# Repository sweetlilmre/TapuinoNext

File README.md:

# TapuinoNext

## Intro

Welcome to the TapuinoNext alpha.  

Most of the code has been written and tested to a fair extent, but there are bound to be loads of bugs.
Please report bugs as issues against the repo. If you have fixes, please submit these as a pull request.
I could really use some help with documentation in markdown format if you would like to contribute in that way.

## Using the TapuinoNext

Instructions on how to navigate the UI and detail on the TapuinoNext functionality can be found on this page: [TapuinoNext UI](docs/ui/TapuinoNext-UI.md). This is still very much a work in progress.

## Hardware

- "instructions" to build a stripboard prototype are available at [Prototype Build](docs/PrototypeBuild.md)
- schematics and board designs for reference implementations are available in the [Eagle](docs/Eagle) folder.
- the mini board has been produced and tested successfully!
- **NB: the micro board has not**

The BOM for the TapuinoNext is:
- ESP32 Devkit equivalent: e.g. https://www.banggood.com/ESP32-WiFi-+-bluetooth-Development-Board-Ultra-Low-Power-Consumption-Dual-Core-ESP-32-ESP-32S-Similar-ESP8266-Geekcreit-for-Arduino-products-that-work-with-official-Arduino-boards-p-1175488.html

- resistors:
  - (voltage divider)
    - 1k5
    - 3k3
  - 100 Ohm (Recording LED current limiter)
- Rotary encoder KY-040: e.g. https://www.banggood.com/5Pcs-5V-KY-040-Rotary-Encoder-Module-AVR-PIC-p-951151.html

- LCD screen: SSD1306 OLED or HD44780 via I2C backpack
- SD Card breakout board / socket, no level shifter! Ones without resistors seem to work better. I used something like this: https://www.mischianti.org/2019/12/15/how-to-use-sd-card-with-esp8266-and-arduino/
This is the one I built:

- Bi-directional level shifter: e.g. https://www.banggood.com/10Pcs-Logic-Level-Converter-Bi-Directional-IIC-4-Way-Level-Conversion-Module-p-1033750.html

- C64 Datasette connector (use one off of a dead datasette or find one of these: https://www.thefuturewas8bit.com/cassette-port-connector-vic20-64-64c-128-128d-pet.html)

Wire this all up according to the schematic and flash the firmware.

## Firmware

If you have already flashed a recent firmware, then firmware releases are available at: https://github.com/sweetlilmre/TapuinoNext/releases

As newer firmware can self update, all you need to do is drop the *update.bin* file onto the root of the SD Card and select the firmware update option from the options menu.

For a first time build:

There is now an alternative to building the code and flashing.
- Download the latest `update.factory.bin` from the [TapuinoNext Releases Page ](https://github.com/sweetlilmre/TapuinoNext/releases)
- Using Google Chrome, go to the [Adafruit ESP Tool](https://adafruit.github.io/Adafruit_WebSerial_ESPTool/) page.
- Connect your ESP32 to your machine and make sure the drivers are installed
- Click "Connect" on the Adafruit page and select the COM port of your ESP32
- If the connect succeeds, you should see several `Choose a file...` buttons
- Click the first one, navigate to and select the `update.factory.bin` file you downloaded
- Click `Program`
- A progress bar will appear, once this is complete you should be good to go

Probably the easiest way to handle this at the moment is to:
- install VS Code
- install Platformio on top of that
- install the Espressif 32 platform or start a new project and choose "Espressif ESP32 Dev Module" as the board, with "Arduino" as the framework
- clone the TapuinoNext repository
- you will need to create a ***config-user.h*** file in the include directory. This is currently used to specify which of the 2 supported displays you have and what the correct I2C address for the display is. A sample ***config-user.h.example*** has beem provided
- point VS code to the directory you cloned the repo into and upload to the board (I'm assuming that you know how to do all of this)

## TODO / Roadmap

See [TODO](TODO.md)

## Attribution

See [Attribution](docs/Attribution.md)

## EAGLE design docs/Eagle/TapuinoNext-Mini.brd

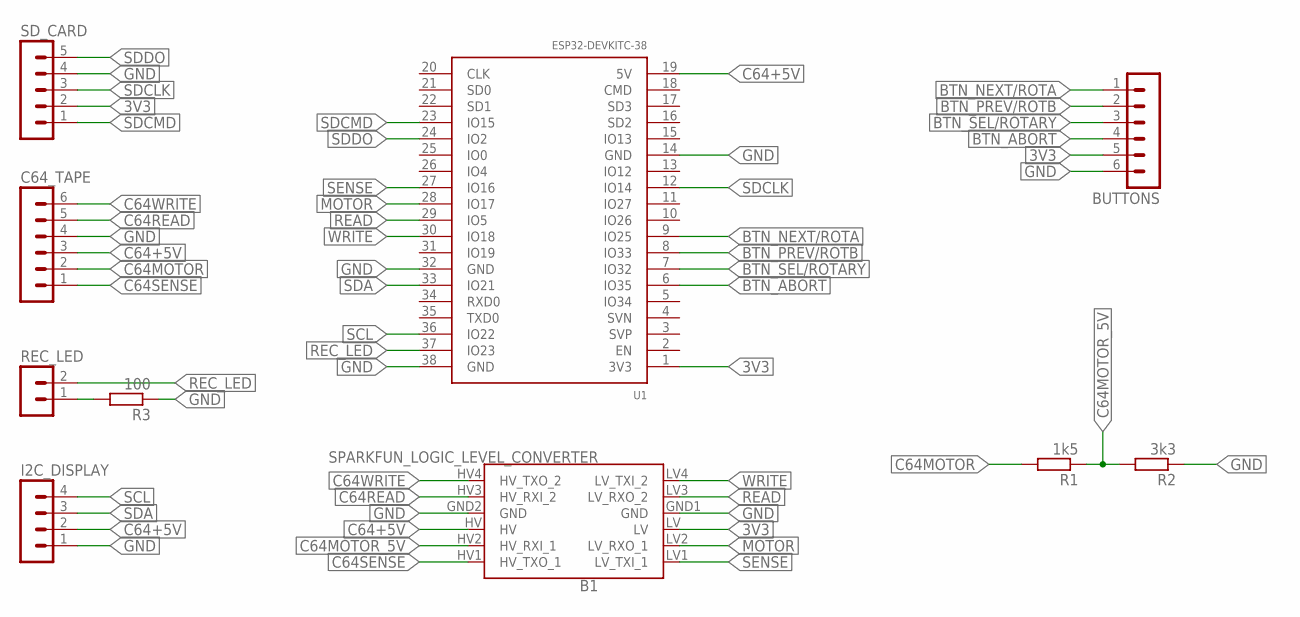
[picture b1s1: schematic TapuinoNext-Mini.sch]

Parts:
B1: SPARKFUN_LOGIC_LEVEL_CONVERTER
BUTTONS: MA06-1
C64_TAPE: MA06-1
I2C_DISPLAY: MA04-1
R1: 1k5; 0207/10
R2: 3k3; 0207/10
R3: 100; 0207/10
REC_LED: MA02-1
SD_CARD: MA05-1
U1: ESP32-DEVKITC-38

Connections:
3V3: B1.LV, BUTTONS.5, SD_CARD.2, U1.1 (3V3)
BTN_ABORT: BUTTONS.4, U1.6 (IO35)
BTN_NEXT/ROTA: BUTTONS.1, U1.9 (IO25)
BTN_PREV/ROTB: BUTTONS.2, U1.8 (IO33)
BTN_SEL/ROTARY: BUTTONS.3, U1.7 (IO32)
C64+5V: B1.HV, C64_TAPE.3, I2C_DISPLAY.2, U1.19 (5V)
C64MOTOR: C64_TAPE.2, R1.2
C64MOTOR_5V: B1.HV2 (HV_RXI_1), R1.1, R2.2
C64READ: B1.HV3 (HV_RXI_2), C64_TAPE.5
C64SENSE: B1.HV1 (HV_TXO_1), C64_TAPE.1
C64WRITE: B1.HV4 (HV_TXO_2), C64_TAPE.6
GND: B1.GND1 (GND), B1.GND2 (GND), BUTTONS.6, C64_TAPE.4, I2C_DISPLAY.1, R2.1, R3.1, SD_CARD.4, U1.14 (GND), U1.32 (GND), U1.38 (GND)
MOTOR: B1.LV2 (LV_RXO_1), U1.28 (IO17)
unnamed: R3.2, REC_LED.1
READ: B1.LV3 (LV_RXO_2), U1.29 (IO5)
REC_LED: REC_LED.2, U1.37 (IO23)
SCL: I2C_DISPLAY.4, U1.36 (IO22)
SDA: I2C_DISPLAY.3, U1.33 (IO21)
SDCLK: SD_CARD.3, U1.12 (IO14)
SDCMD: SD_CARD.1, U1.23 (IO15)
SDDO: SD_CARD.5, U1.24 (IO2)
SENSE: B1.LV1 (LV_TXI_1), U1.27 (IO16)
WRITE: B1.LV4 (LV_TXI_2), U1.30 (IO18)

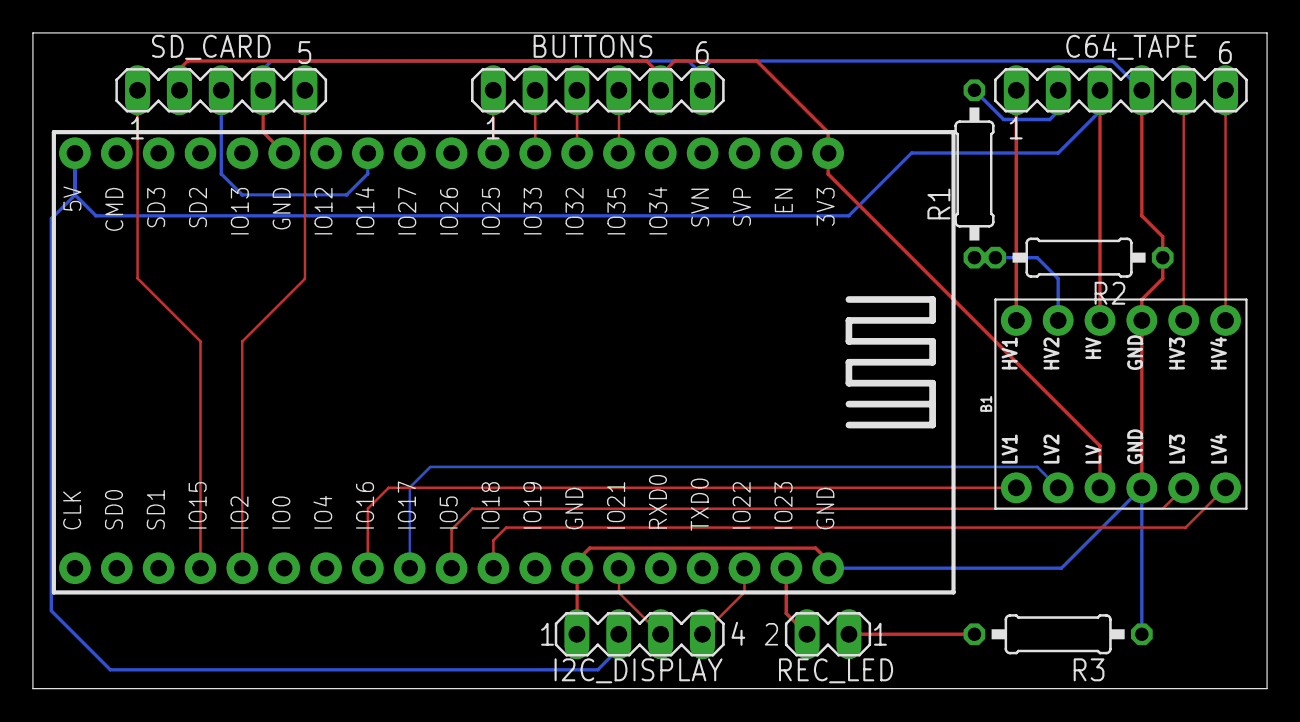
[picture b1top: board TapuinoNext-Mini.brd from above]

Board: 2 copper layers, 74.9 x 39.8 mm, 10 parts (0 on the bottom side), 23 nets.

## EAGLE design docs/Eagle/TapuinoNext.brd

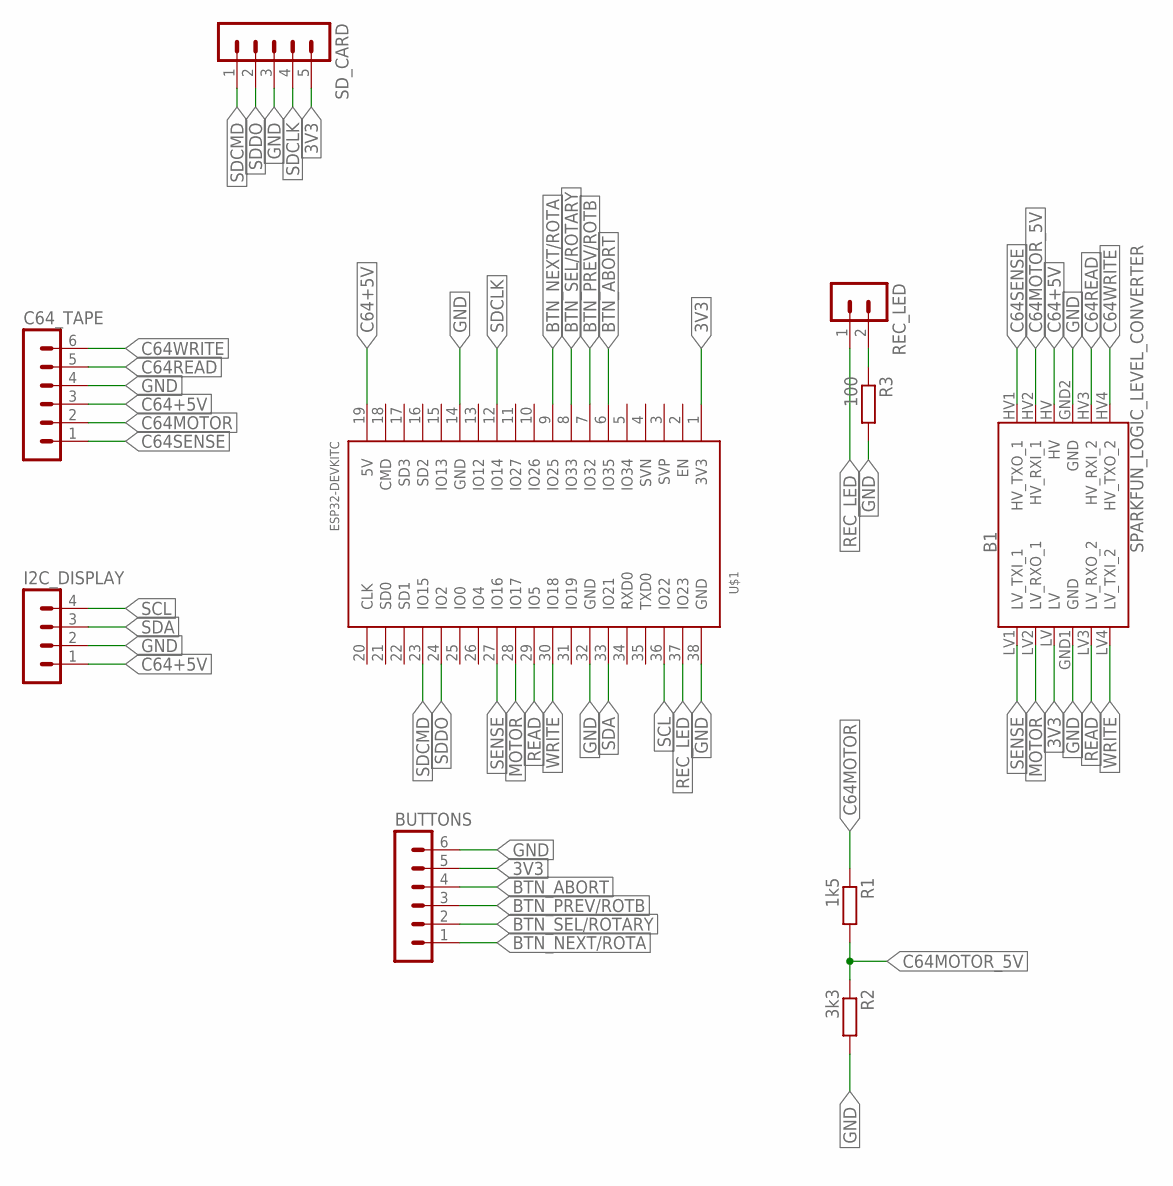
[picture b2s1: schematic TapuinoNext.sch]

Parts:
B1: SPARKFUN_LOGIC_LEVEL_CONVERTER
BUTTONS: MA06-1
C64_TAPE: MA06-1
I2C_DISPLAY: MA04-1
R1: 1k5; 0204/7
R2: 3k3; 0204/7
R3: 100; 0204/7
REC_LED: MA02-1
SD_CARD: MA05-1
U$1: ESP32DEVKITC; ESP32-DEVKITC

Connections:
3V3: B1.LV, BUTTONS.5, SD_CARD.5, U$1.1 (3V3)
BTN_ABORT: BUTTONS.4, U$1.6 (IO35)
BTN_NEXT/ROTA: BUTTONS.1, U$1.9 (IO25)
BTN_PREV/ROTB: BUTTONS.3, U$1.7 (IO32)
BTN_SEL/ROTARY: BUTTONS.2, U$1.8 (IO33)
C64+5V: B1.HV, C64_TAPE.3, I2C_DISPLAY.1, U$1.19 (5V)
C64MOTOR: C64_TAPE.2, R1.1
C64MOTOR_5V: B1.HV2 (HV_RXI_1), R1.2, R2.1
C64READ: B1.HV3 (HV_RXI_2), C64_TAPE.5
C64SENSE: B1.HV1 (HV_TXO_1), C64_TAPE.1
C64WRITE: B1.HV4 (HV_TXO_2), C64_TAPE.6
GND: B1.GND1 (GND), B1.GND2 (GND), BUTTONS.6, C64_TAPE.4, I2C_DISPLAY.2, R2.2, R3.2, SD_CARD.3, U$1.14 (GND), U$1.32 (GND), U$1.38 (GND)
MOTOR: B1.LV2 (LV_RXO_1), U$1.28 (IO17)
unnamed: R3.1, REC_LED.2
READ: B1.LV3 (LV_RXO_2), U$1.29 (IO5)
REC_LED: REC_LED.1, U$1.37 (IO23)
SCL: I2C_DISPLAY.4, U$1.36 (IO22)
SDA: I2C_DISPLAY.3, U$1.33 (IO21)
SDCLK: SD_CARD.4, U$1.12 (IO14)
SDCMD: SD_CARD.1, U$1.23 (IO15)
SDDO: SD_CARD.2, U$1.24 (IO2)
SENSE: B1.LV1 (LV_TXI_1), U$1.27 (IO16)
WRITE: B1.LV4 (LV_TXI_2), U$1.30 (IO18)

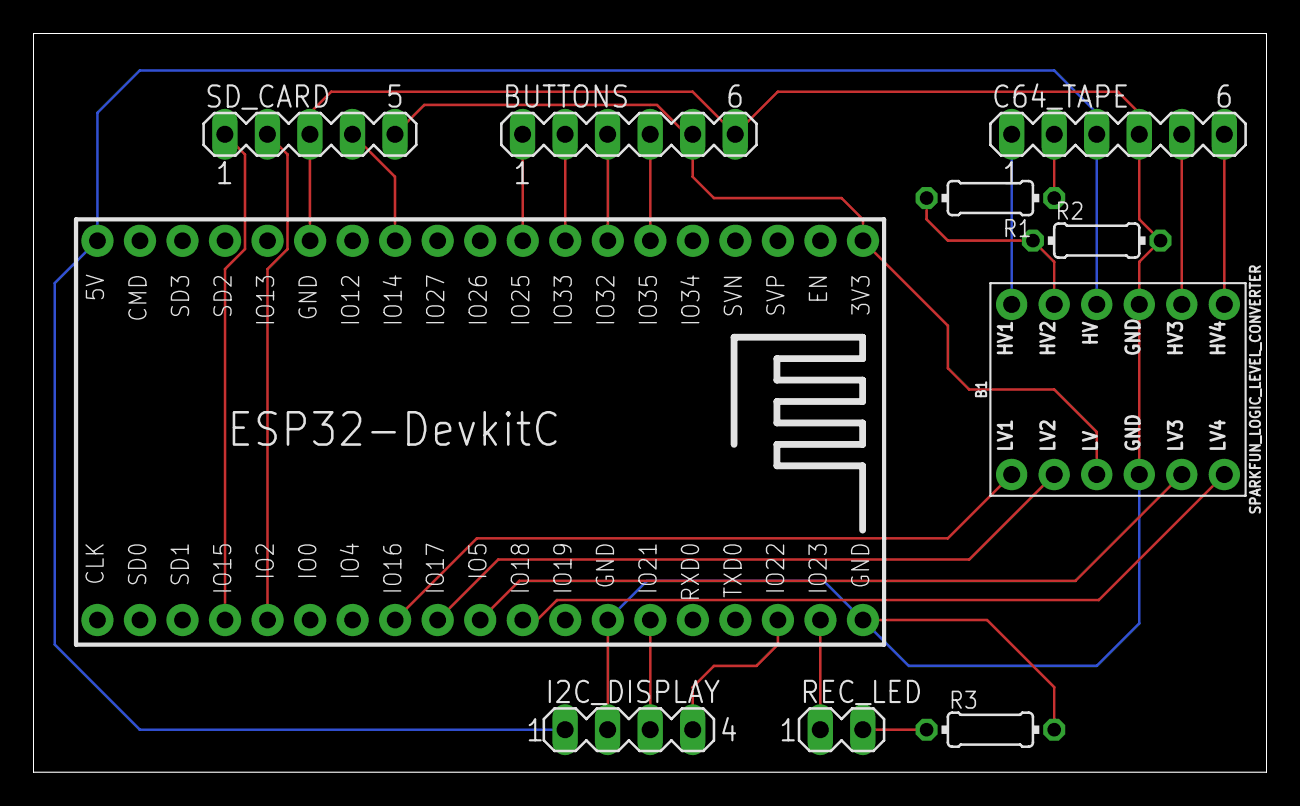
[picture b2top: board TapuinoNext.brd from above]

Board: 2 copper layers, 73.6 x 44.1 mm, 10 parts (0 on the bottom side), 23 nets.

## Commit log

2021-07-19 TapuinoNext first alpha commit
2021-07-19 Added basic instructions into the readme
2021-08-02 - added some serial messages for circuit debugging. - begining rotoarty rework
2021-08-18 Added loads of documentation
2021-08-18 Added reference board silkscreen (c) text
2021-08-18 added attribution link to readme
2021-08-18 added direct links for attribution files
2021-08-18 add rec led and tidied up the board / schematic
2021-08-18 Added 2 pin part for record LED
2021-08-25 fixed definition for OLED1306 added the correct part for tthe ESP32 Devkit added a micro board for system builders (trying to keep this to the smallest footprint possible for custom builds) fixed the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
2021-08-25 NOTE: enoder pins have CHANGED, please update your builds accordingly
2021-08-25 Fixed wiring for rotarty in Fritzing sketch
2021-08-26 Changed rotary wiring back to original to match stripboard
2021-08-26 updated pdf of schematic to reflect changes
2021-08-26 update stripboard files (added led) updated fritzing files (added led) added legend for stripboard prototype
2021-08-26 fix? prototype build doc
2021-08-26 Update PrototypeBuild.md
    fixed PNGs display (damn upper case extension :( )
2021-09-02 Fixed pinout across all of the schematics, hopefully for the last time
2021-09-17 - rewrote some of the options code seems to fix a heap corruption error - fixed a bug in the options menu handling copypasta on the wrong class type - updated the documentation the mini board has now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
2021-09-20 added mini reference board image
2021-09-20 resized image
2022-03-11 First attempt to add build actions
2022-03-11 next ci attempt
2022-03-11 add ci step to generate config-user.h
2022-03-11 Attempting ci auto release
2022-03-11 ci release test2
2022-03-11 added tag trigger for ci test
2022-03-11 updating release details
2022-03-11 more ci tests
2022-03-11 testing more commit history
2022-03-15 basic update from sd code, not tested
2022-03-15 added git tag based versioning
2022-03-15 basic update from sd code, not tested (#1)
2022-03-16 Added auto build version
2022-03-17 testing badges
2022-03-17 auto release script with tagging added
2022-03-17 added more sanity checking to release script
2022-03-17 Adding interactivity options to release script
2022-03-17 Added option to push pending commits to release script
2022-03-17 minor cleanup
2022-03-17 minor cleanup #2
2022-03-17 python != c
2022-03-17 version bump
2022-03-17 version bump again
2022-03-17 Testing new release action
2022-03-17 fixing version in release action
2022-03-18 Initial FW updater code complete and tested
2022-04-03 fixed newlines in auto_version.py
2022-05-03 initial tapecart test
2022-05-03 Fixed recording issue Cleaned up some code Starterd on some user documentation
2022-05-03 Fixed recording, several build script improvement and some general cleanup
2022-05-05 Fixed Platformio version to 4.1.0 to avoid 4.2.0 broken timer behaviour
2022-06-04 Fixed various compatibility issues with framework-arduinoespressif32 > 2.0.1 - the platform is pinned to version 4.0.1 (and hence framework 2.0.1) waiting for timer fixes to get into the next framewo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
    Other minor improvments
    - changed the text for the firmware update menu to make it less confusing
    - added the spinner UI into the update prog
2022-06-04 Fixed line endings in RELEASE_NOTES
2022-06-04 Moved release notes to the right place
2022-06-04 Moving release notes
2022-06-04 testing release notes
2022-06-09 Minor changes to how version and releases work.
2022-06-09 more version and release changes
2022-06-09 missed build gate for release notes
2022-06-09 more release note fixes
2022-06-09 again
2022-06-09 again again
2022-06-09 test ls
2022-06-09 woohoo! releasenotes work!
2022-06-10 commenting tapecart stuff for main merge
2022-06-10 minor readme changes
2022-06-10 Fixed version handling for actions and added auto change log (#3)
    * initial tapecart test
    * Minor changes to how version and releases work.
    * more version and release changes
    * missed build gate for release notes
    * more release note fixes
    * again
2022-06-14 Moved buffer handling to FlipBuffer
2022-06-16 name->path mismatch
2022-06-16 no .* files exept ".." in LoadSelector
2022-06-16 empty line removed
2022-06-20 Initial functional implementation of TapeCartLoader and other minor fixes
2022-06-21 Cleanup of unused paramaters
2022-06-21 Minor cleanup of comments etc.
2022-06-22 name->path mismatch (#7)
    Looks great, thank for your contribution
2022-06-22 updated release notes
2022-06-22 Tape cart impl (#4)
    * initial tapecart test
    * Minor changes to how version and releases work.
    * more version and release changes
    * missed build gate for release notes
    * more release note fixes
    * woohoo! releasenotes work!
2022-06-22 Release v0.0.3-alpha+240 version bump
2022-07-05 Implemented PRG loading changes
2022-07-17 Display Size of HD44780 can be 20x4. Default is 16x2
2022-07-21 Display Size configuration 2nd try
2022-09-12 Display Size configuration 2nd try (#9)
    Apologies for the long delay in merging this. Life got in the way :)
2022-11-17 Still working on tapecart loader
2022-12-06 Updated build scripts to generate a full binary flash image for use with web flashers Updated github actions to upload the full flash image Updates github actions to use later versions
2022-12-06 Fixed action version problem
2022-12-06 testing action based full bin build
2022-12-06 more packing testing
2022-12-07 Added factory image script back, updated attibution to reflect origin
2022-12-07 Retry commit
2022-12-07 test
2022-12-08 Fishing touches for creating update.factory.bin

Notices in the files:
docs/Eagle/TapuinoNext-Mini.brd:
(c) 2021 sweetlilmre
docs/Eagle/TapuinoNext.brd:
TapuinoNext (c) 2021 sweetlilmre
parts and their libraries:
SparkFun-Boards: Licensing: Creative Commons ShareAlike 4.0 International - https://creativecommons.org/licenses/by-sa/4.0
